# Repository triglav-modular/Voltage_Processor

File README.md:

# Triglav Modular Voltage Processor
Eurorack voltage processor / ring modulator inspired by the Buchla 257.

Features:

* Two independent channels, each mixing an attenuverter, a voltage-controlled crossfader and an offset voltage (0-5V).
* „Ring” switches turn the crossfaders into ring modulators / bipolar VCAs.
* S-curve attenuverters for easier nulling.
* Can be trimmed precisely for 1V/oct signals
* LEDs indicating negative/positive voltage.

Other notes:
* Crossfader expects a 0-8V envelope in regular mode.
* Turning on the ring switch normalizes an inverted copy of the inputs into each other. This allows the crossfader to be used as a second attenuverter, a bipolar VCA or a ring modulator with adjustable bias without any additonal patching.
* 11 HP, compact design
* Panel + PCB sandwich, suitable for skiffs
* Reverse polarity protection
* Open source

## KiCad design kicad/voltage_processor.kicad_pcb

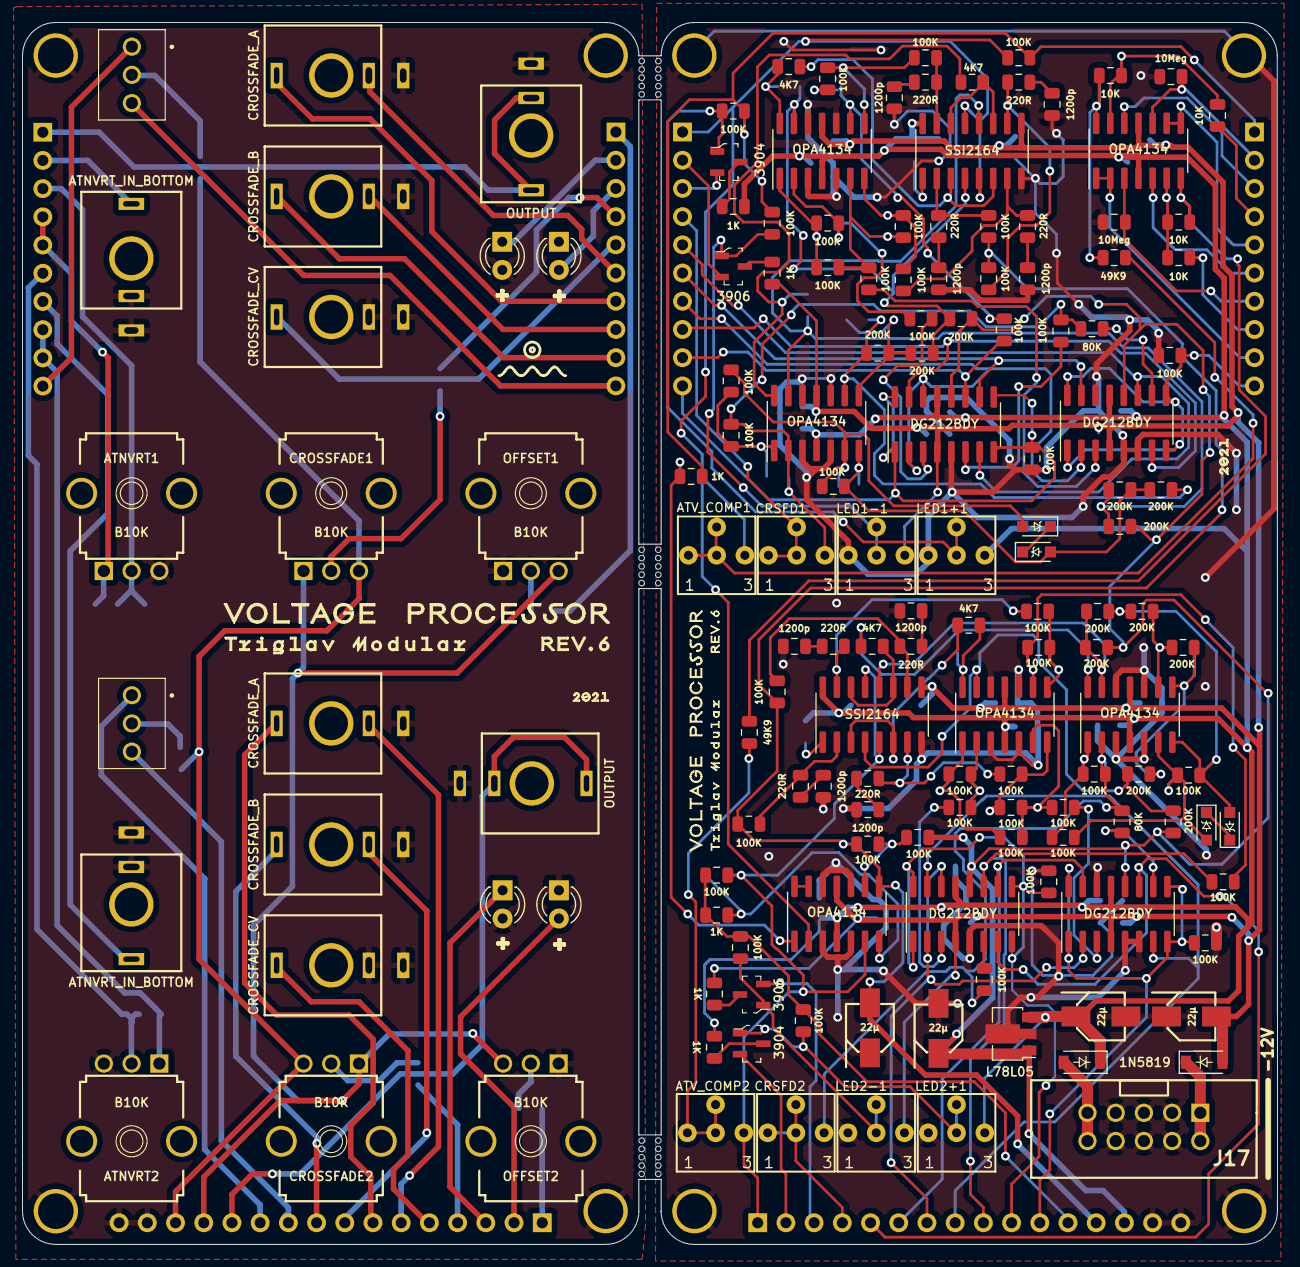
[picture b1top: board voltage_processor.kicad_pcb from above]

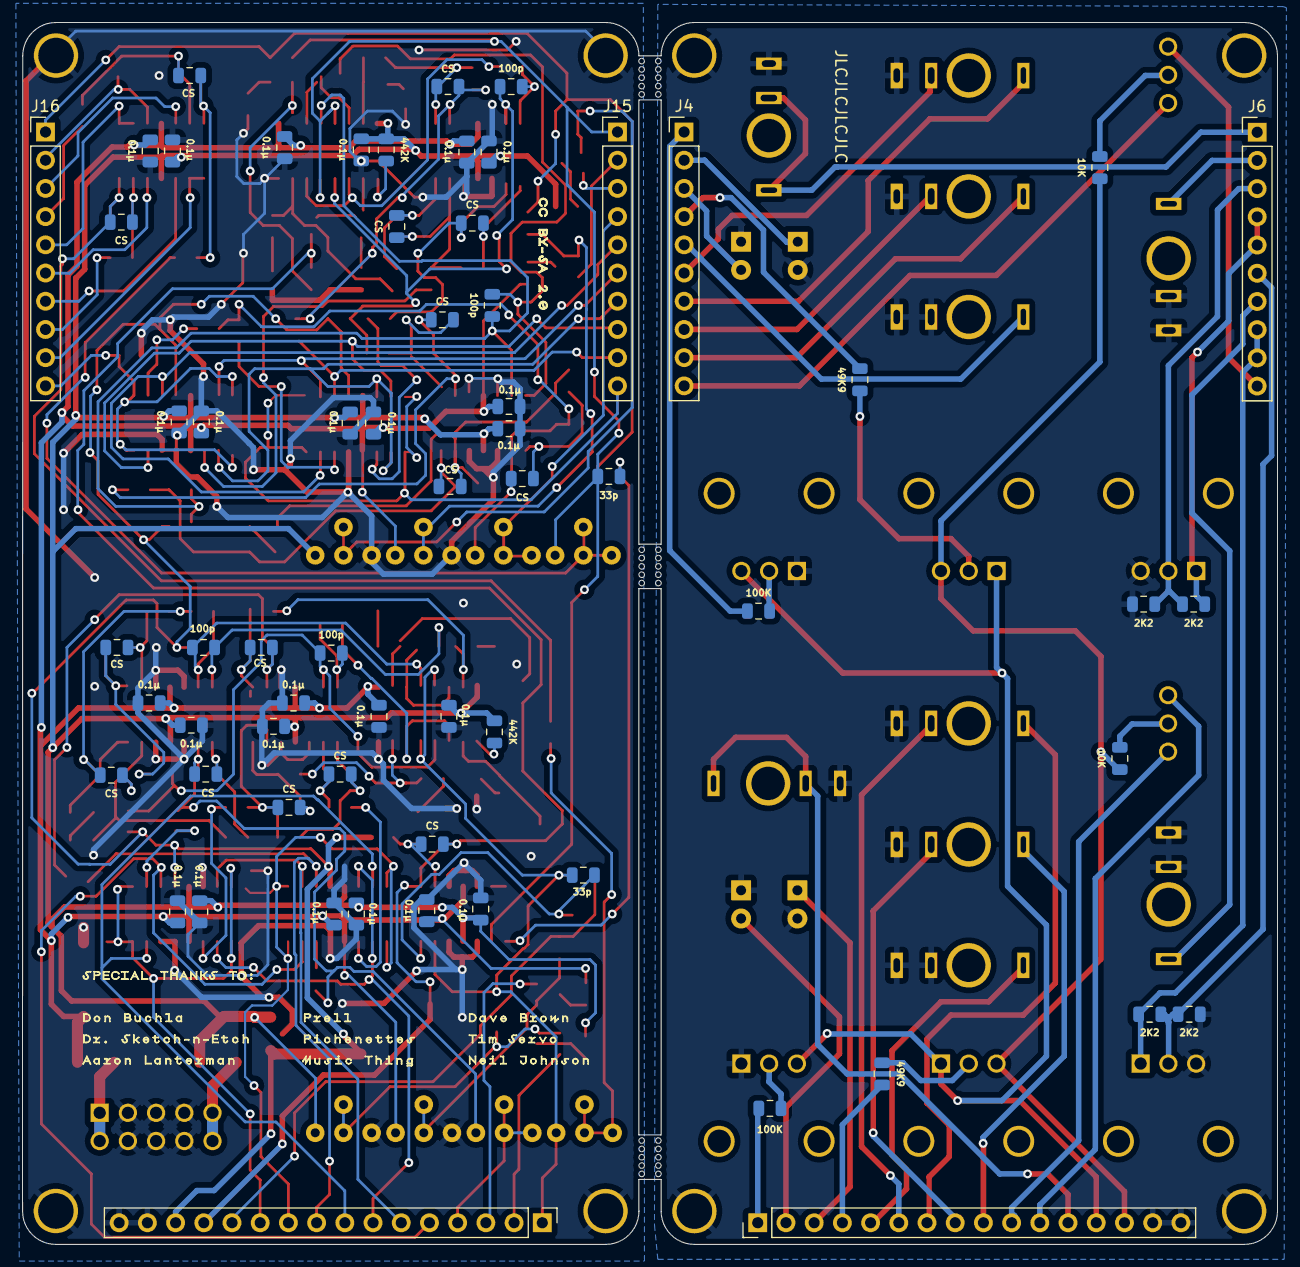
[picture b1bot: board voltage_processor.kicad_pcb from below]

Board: 2 copper layers, 113.0 x 110.0 mm, 222 parts (63 on the bottom side), 160 nets.

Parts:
ATNVRT1, ATNVRT2: B10K; MusicThingModular-9MM_SNAP-IN_POT
ATV_COMP1, ATV_COMP2: 100K; BOURNS_3362P_TRIMMER
C1, C2, C3, C4: 22µ; CAPAE430X610N
C5, C6, C18, C19, C20, C21, C22, C23, C24, C25, C35, C36, C37, C38, C45, C46, C51, C52, C55, C56, C61, C62, C67, C68: 0.1µ; C_0805_2012Metric
C7, C8, C17, C42, C43, C47, C48, C49, C50, C58, C59, C63, C64, C65, C66: CS; C_0805_2012Metric
C10, C12, C27, C29: 100p; C_0805_2012Metric
C11, C13, C14, C15, C28, C30, C31, C32: 1200p; C_0805_2012Metric
C54, C70: 33p; C_0805_2012Metric
CROSSFADE1, CROSSFADE2: B10K; MusicThingModular-9MM_SNAP-IN_POT
CRSFD1, CRSFD2: 100K; BOURNS_3362P_TRIMMER
D1, D2: 1N5819; D_SOD-123
D3, D4, D5, D6: LED; LED_D3.0mm
D7, D8, D9, D10: Z-5V; D_SOD-323_HandSoldering_ZENER
IC1, IC2, IC3, IC4: DG212BDY; SOIC-16_3.9x9.9mm_P1.27mm
J1, J2: ATNVRT_IN_BOTTOM; THONKICONN
J3: Conn_01x16_Female; PinHeader_1x16_P2.54mm_Vertical
J4, J6: Conn_01x10_Female; PinHeader_1x10_P2.54mm_Vertical
J5: Conn_01x16_Male; PinHeader_1x16_P2.54mm_Vertical
J7, J11: CROSSFADE_CV; THONKICONN
J8, J12: CROSSFADE_A; THONKICONN
J9, J13: CROSSFADE_B; THONKICONN
J10, J14: OUTPUT; THONKICONN
J15, J16: Conn_01x10_Male; PinHeader_1x10_P2.54mm_Vertical
J17: 30310-6002HB; SHDR10W64P254_2X5_2030X878X930P
LED1+1, LED1-1, LED2+1, LED2-1: 100K; BOURNS_3362P_TRIMMER
MH1, MH2, MH3, MH4, MH5, MH6, MH7, MH8: MountingHole_3.2mm_M3
OFFSET1, OFFSET2: B10K; MusicThingModular-9MM_SNAP-IN_POT
Q1, Q3: 3906; SOT-23-3
Q2, Q4: 3904; SOT-23-3
R1, R2, R3, R4: 2K2; R_0805_2012Metric
R5, R6, R7, R8, R89, R104: 10K; R_0805_2012Metric
R9, R32: 10Meg; R_0805_2012Metric
R10, R11, R12, R13, R15, R18, R19, R22, R24, R26, R27, R29, R34, R35, R38, R40, R41, R42, R43, R46, R47, R50, R51, R52, R53, R54, R56, R59, R60, R62, R63, R65, R67, R68, R70, R73, R75, R76, R82, R87, R88, R95, R102, R103: 100K; R_0805_2012Metric
R14, R16, R17, R20, R23, R25, R55, R57, R58, R61, R64, R66: 200K; R_0805_2012Metric
R21, R44, R48, R49, R85, R90: 1K; R_0805_2012Metric
R28, R30, R31, R33, R69, R71, R72, R74: 220R; R_0805_2012Metric
R36, R39: 80K; R_0805_2012Metric
R37, R45, R78, R96: 49K9; R_0805_2012Metric
R105, R106, R108, R109: 4K7; R_0805_2012Metric
R107, R110: 442K; R_0805_2012Metric
S1, S2: 108-2MS1T1B1M2QE-EVX; 1082MS1T1B1M2QEEVX
U1, U4, U5, U8, U9, U11: OPA4134; SOIC-14_3.9x8.7mm_P1.27mm
U2: L78L05; SOT-89-3
U6, U10: SSI2164; SOIC-16_3.9x9.9mm_P1.27mm
mouse-bite-2mm-slot_1, mouse-bite-2mm-slot_2, mouse-bite-2mm-slot_3: VAL**; mouse-bite-2mm-slot

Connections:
+5V: C1.1, IC1.12 (VL), IC2.12 (VL), IC3.12 (VL), IC4.12 (VL), J5.14, R16.2, R25.2, R40.2, R57.2, R66.2, U2.1 (OUT)
+12V: C3.1, C5.1, C18.1, C20.1, C22.1, C35.1, C37.1, C45.1, C46.2, C51.1, C61.1, C62.2, C67.1, D1.1 (K), IC1.13 (V+), IC2.13 (V+), IC3.13 (V+), IC4.13 (V+), LED1+1.3, LED2+1.3, R49.1, R90.1, R107.2, R110.2, U1.4 (V+), U2.3 (IN), U4.4 (V+), U5.4 (V+), U6.16 (V+), U8.4 (V+), U9.4 (V+), U10.16 (V+), U11.4 (V+)
-5V: C2.2, C17.1, J5.13, R29.2, R34.2, R43.1, R70.2, R75.2, U11.8
-12V: C4.2, C6.1, C19.1, C21.1, C23.1, C24.1, C25.1, C36.1, C38.1, C52.1, C55.1, C56.1, C68.1, D2.2 (A), IC1.4 (V-), IC2.4 (V-), IC3.4 (V-), IC4.4 (V-), LED1-1.3, LED2-1.3, R44.1, R85.1, U1.11 (V-), U4.11 (V-), U5.11 (V-), U6.9 (V-), U8.11 (V-), U9.11 (V-), U10.9 (V-), U11.11 (V-)
/Voltage Processor A/ATNVRT_1_M: J16.5, R6.2
/Voltage Processor A/ATNVRT_1_P: ATNVRT1.1 (A), J6.5, J6.6, R3.1
/Voltage Processor A/ATNVRT_2_M: J16.4, U1.12 (+)
/Voltage Processor A/ATNVRT_2_P: ATNVRT1.2 (S), J6.4, R3.2, R4.1
/Voltage Processor A/BUFF_M: J16.3, R32.1, U1.10 (+)
/Voltage Processor A/BUFF_O_M: J16.6, U1.8, U1.9 (-)
/Voltage Processor A/BUFF_P: J2.3, J6.3
/Voltage Processor A/CROSSFADE_A: IC1.2 (D1), IC1.14 (S2), IC2.2 (D1), J15.7
/Voltage Processor A/CROSSFADE_A_NORMAL: IC2.3 (S1), R19.2
/Voltage Processor A/CROSSFADE_A_RING: IC1.3 (S1), R11.2
/Voltage Processor A/CROSSFADE_B: IC1.11 (S3), J15.9, R18.2
/Voltage Processor A/CRSFD_A_1_M: IC1.10 (D3), IC2.15 (D2), J15.6
/Voltage Processor A/CRSFD_A_1_P: J4.6, J8.2
/Voltage Processor A/CRSFD_A_2_P: J4.7, J8.3
/Voltage Processor A/CRSFD_B_1_M: IC1.15 (D2), IC2.7 (D4), J15.8
/Voltage Processor A/CRSFD_B_1_P: J4.8, J9.2
/Voltage Processor A/CRSFD_B_2_P: J4.9, J9.3
/Voltage Processor A/CRSFD_CV_M: IC1.7 (D4), IC2.11 (S3), J15.5
/Voltage Processor A/CRSFD_CV_NORMAL: IC2.10 (D3), R39.2
/Voltage Processor A/CRSFD_CV_P: J4.5, J7.3
/Voltage Processor A/CRSFD_CV_RING: IC1.6 (S4), R38.1
/Voltage Processor A/CRSFD_POT_M: CRSFD1.1, CRSFD1.2, J15.4
/Voltage Processor A/CRSFD_POT_P: J4.4, R96.1
/Voltage Processor A/LED_NEG_M: J15.2, Q3.2 (E)
/Voltage Processor A/LED_NEG_P: D3.1 (K), J4.2
/Voltage Processor A/LED_POS_M: J15.3, Q4.2 (E)
/Voltage Processor A/LED_POS_P: D4.2 (A), J4.3
/Voltage Processor A/OFFSET_M: ATV_COMP1.3, C70.2, J15.1, R46.2, U6.5 (I_OUT2), U6.13 (I_OUT4), U11.2 (-)
/Voltage Processor A/OFFSET_P: J4.1, R76.2
/Voltage Processor A/OUTPUT_M: J16.2, R41.2, R46.1, R47.2, R48.1
/Voltage Processor A/OUTPUT_P: J6.2, J10.2, J10.3
/Voltage Processor A/RING_OFF: IC2.1 (IN1), IC2.8 (IN4), IC2.9 (IN3), IC2.16 (IN2), J16.1, R103.2
/Voltage Processor A/RING_OFF_P: J6.1, S2.1
/Voltage Processor A/RING_ON: IC1.1 (IN1), IC1.8 (IN4), IC1.9 (IN3), IC1.16 (IN2), J15.10, R73.2
/Voltage Processor A/RING_ON_P: J4.10, S2.3
/Voltage Processor B/ATNVRT_1_M: J16.9, R5.2
/Voltage Processor B/ATNVRT_1_P: ATNVRT2.1 (A), J6.9, J6.10, R1.1
/Voltage Processor B/ATNVRT_2_M: J16.7, U1.5 (+)
/Voltage Processor B/ATNVRT_2_P: ATNVRT2.2 (S), J6.7, R1.2, R2.1
/Voltage Processor B/BUFF_M: J16.8, R9.1, U1.3 (+)
/Voltage Processor B/BUFF_O_M: J16.10, U1.1, U1.2 (-)
/Voltage Processor B/BUFF_P: J1.3, J6.8
/Voltage Processor B/CROSSFADE_A: IC3.2 (D1), IC3.14 (S2), IC4.2 (D1), J5.7
/Voltage Processor B/CROSSFADE_A_NORMAL: IC4.3 (S1), R60.2
/Voltage Processor B/CROSSFADE_A_RING: IC3.3 (S1), R52.2
/Voltage Processor B/CROSSFADE_B: IC3.11 (S3), J5.9, R59.2
/Voltage Processor B/CRSFD_A_1_M: IC3.10 (D3), IC4.15 (D2), J5.6
/Voltage Processor B/CRSFD_A_1_P: J3.6, J12.2
/Voltage Processor B/CRSFD_A_2_P: J3.7, J12.3
/Voltage Processor B/CRSFD_B_1_M: IC3.15 (D2), IC4.7 (D4), J5.8
/Voltage Processor B/CRSFD_B_1_P: J3.8, J13.2
/Voltage Processor B/CRSFD_B_2_P: J3.9, J13.3
/Voltage Processor B/CRSFD_CV_M: IC3.7 (D4), IC4.11 (S3), J5.5
/Voltage Processor B/CRSFD_CV_NORMAL: IC4.10 (D3), R36.2
/Voltage Processor B/CRSFD_CV_P: J3.5, J11.3
/Voltage Processor B/CRSFD_CV_RING: IC3.6 (S4), R35.1
/Voltage Processor B/CRSFD_POT_M: CRSFD2.1, CRSFD2.2, J5.4
/Voltage Processor B/CRSFD_POT_P: J3.4, R45.1
/Voltage Processor B/LED_NEG_M: J5.3, Q1.2 (E)
/Voltage Processor B/LED_NEG_P: D5.1 (K), J3.3
/Voltage Processor B/LED_POS_M: J5.2, Q2.2 (E)
/Voltage Processor B/LED_POS_P: D6.2 (A), J3.2
/Voltage Processor B/OFFSET_M: ATV_COMP2.3, C54.2, J5.1, R87.2, U10.5 (I_OUT2), U10.13 (I_OUT4), U11.6 (-)
/Voltage Processor B/OFFSET_P: J3.1, R42.2
/Voltage Processor B/OUTPUT_M: J5.12, R21.1, R82.2, R87.1, R88.2
/Voltage Processor B/OUTPUT_P: J3.12, J14.2, J14.3
/Voltage Processor B/RING_OFF: IC4.1 (IN1), IC4.8 (IN4), IC4.9 (IN3), IC4.16 (IN2), J5.11, R62.2
/Voltage Processor B/RING_OFF_P: J3.11, S1.1
/Voltage Processor B/RING_ON: IC3.1 (IN1), IC3.8 (IN4), IC3.9 (IN3), IC3.16 (IN2), J5.10, R50.2
/Voltage Processor B/RING_ON_P: J3.10, S1.3
GND: C1.2, C2.1, C3.2, C4.1, C5.2, C6.2, C11.1, C13.1, C14.1, C15.1, C18.2, C19.2, C20.2, C21.2, C22.2, C23.2, C24.2, C25.2, C28.1, C30.1, C31.1, C32.1, C35.2, C36.2, C37.2, C38.2, C45.2, C46.1, C51.2, C52.2, C55.2, C56.2, C61.2, C62.1, C67.2, C68.2, IC1.5 (GND), IC2.5 (GND), IC2.6 (S4), IC2.14 (S2), IC3.5 (GND), IC4.5 (GND), IC4.6 (S4), IC4.14 (S2), J5.15, J5.16, J17.3, J17.4, J17.5, J17.6, J17.7, J17.8, LED1+1.1, LED1-1.1, LED2+1.1, LED2-1.1, R9.2, R32.2, R50.1, R62.1, R73.1, R103.1, U2.2 (GND), U4.3 (+), U4.5 (+), U4.10 (+), U4.12 (+), U5.3 (+), U5.5 (+), U5.10 (+), U5.12 (+), U6.8 (GND), U8.3 (+), U8.5 (+), U8.10 (+), U8.12 (+), U9.3 (+), U9.5 (+), U9.10 (+), U9.12 (+), U10.8 (GND), U11.3 (+), U11.5 (+), U11.10 (+), U11.12 (+)
GND1: ATNVRT1.3 (E), ATNVRT2.3 (E), D3.2 (A), D4.1 (K), D5.2 (A), D6.1 (K), J1.1, J1.2, J2.1, J2.2, J3.15, J3.16, J7.1, J7.2, J8.1, J9.1, J10.1, J11.1, J11.2, J12.1, J13.1, J14.1, OFFSET1.1 (A), OFFSET2.1 (A), R2.2, R4.2
unnamed: ATV_COMP1.1, ATV_COMP1.2, R37.1
unnamed: ATV_COMP2.1, ATV_COMP2.2, R78.1
unnamed: C7.1, R8.1, R37.2, U1.14
unnamed: C7.2, R6.1, R8.2, U1.13 (-)
unnamed: C8.1, R7.1, R78.2, U1.7
unnamed: C8.2, R5.1, R7.2, U1.6 (-)
unnamed: C10.1, R109.2, U4.14
unnamed: C10.2, R14.1, R16.1, U4.13 (-), U6.12 (I_OUT3)
unnamed: C11.2, R28.2
unnamed: C12.1, R108.1, U5.14
unnamed: C12.2, R23.1, R25.1, U5.13 (-), U6.4 (I_OUT1)
unnamed: C13.2, R30.2
unnamed: C14.2, R31.2
unnamed: C15.2, R33.2
unnamed: C17.2, R40.1, R43.2, U11.9 (-)
unnamed: C27.1, R106.2, U8.14
unnamed: C27.2, R55.1, R57.1, U8.13 (-), U10.12 (I_OUT3)
unnamed: C28.2, R69.2
unnamed: C29.1, R105.1, U9.14
unnamed: C29.2, R64.1, R66.1, U9.13 (-), U10.4 (I_OUT1)
unnamed: C30.2, R71.2
unnamed: C31.2, R72.2
unnamed: C32.2, R74.2
unnamed: C42.1, R51.1, R53.2, U8.1
unnamed: C42.2, CRSFD2.3, R35.2, R36.1, R51.2, U8.2 (-)
unnamed: C43.1, R54.1, R95.2, U9.1
unnamed: C43.2, R52.1, R54.2, U9.2 (-)
unnamed: C47.1, D7.2 (A), R55.2, R56.1, R58.2, U8.7
unnamed: C47.2, D8.2 (A), R53.1, R56.2, U8.6 (-)
unnamed: C48.1, R61.1, R64.2, U8.8
unnamed: C48.2, R58.1, R61.2, U8.9 (-)
unnamed: C49.1, R63.1, R67.2, U9.8
unnamed: C49.2, R59.1, R63.2, U9.9 (-)
unnamed: C50.1, R65.1, R68.2, U9.7
unnamed: C50.2, R60.1, R65.2, R95.1, U9.6 (-)
unnamed: C54.1, R21.2, U11.7
unnamed: C58.1, R10.1, R12.2, U4.1
unnamed: C58.2, CRSFD1.3, R10.2, R38.2, R39.1, U4.2 (-)
unnamed: C59.1, R13.1, R102.2, U5.1
unnamed: C59.2, R11.1, R13.2, U5.2 (-)
unnamed: C63.1, D9.2 (A), R14.2, R15.1, R17.2, U4.7
unnamed: C63.2, D10.2 (A), R12.1, R15.2, U4.6 (-)
unnamed: C64.1, R20.1, R23.2, U4.8
unnamed: C64.2, R17.1, R20.2, U4.9 (-)
unnamed: C65.1, R22.1, R26.2, U5.8
unnamed: C65.2, R18.1, R22.2, U5.9 (-)
unnamed: C66.1, R24.1, R27.2, U5.7
unnamed: C66.2, R19.1, R24.2, R102.1, U5.6 (-)
unnamed: C70.1, R48.2, U11.1
unnamed: CROSSFADE1.2 (S), R96.2
unnamed: CROSSFADE2.2 (S), R45.2
unnamed: D1.2 (A), J17.9, J17.10
unnamed: D2.1 (K), J17.1, J17.2
unnamed: D7.1 (K), D8.1 (K)
unnamed: D9.1 (K), D10.1 (K)
unnamed: LED1+1.2, Q4.1 (B), R47.1
unnamed: LED1-1.2, Q3.1 (B), R41.1
unnamed: LED2+1.2, Q2.1 (B), R88.1
unnamed: LED2-1.2, Q1.1 (B), R82.1
unnamed: OFFSET1.2 (S), R76.1
unnamed: OFFSET2.2 (S), R42.1
unnamed: Q1.3 (C), R85.2
unnamed: Q2.3 (C), R90.2
unnamed: Q3.3 (C), R44.2
unnamed: Q4.3 (C), R49.2
unnamed: R26.1, R28.1, U6.15 (I_IN4)
unnamed: R27.1, R30.1, U6.7 (I_IN2)
unnamed: R29.1, R31.1, U6.10 (I_IN3)
unnamed: R33.1, R34.1, U6.2 (I_IN1)
unnamed: R67.1, R69.1, U10.15 (I_IN4)
unnamed: R68.1, R71.1, U10.7 (I_IN2)
unnamed: R70.1, R72.1, U10.10 (I_IN3)
unnamed: R74.1, R75.1, U10.2 (I_IN1)
unnamed: R89.1, S1.2 (COM)
unnamed: R104.1, S2.2 (COM)
unnamed: R105.2, U10.3 (VC1), U10.6 (VC2)
unnamed: R106.1, U10.11 (VC3), U10.14 (VC4)
unnamed: R107.1, U10.1 (MODE)
unnamed: R108.2, U6.3 (VC1), U6.6 (VC2)
unnamed: R109.1, U6.11 (VC3), U6.14 (VC4)
unnamed: R110.1, U6.1 (MODE)
unnamed: U11.13 (-), U11.14
PANEL_+5V: CROSSFADE1.3 (E), CROSSFADE2.3 (E), J3.14, R89.2, R104.2
PANEL_-5V: CROSSFADE1.1 (A), CROSSFADE2.1 (A), J3.13, OFFSET1.3 (E), OFFSET2.3 (E)

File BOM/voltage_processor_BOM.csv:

"Id";"Designator";"Package";"Quantity";"Designation";"Supplier and ref";
1;"R26,R68,R75,R22,R102,R63,R103,R10,R19,R15,R52,R38,R18,R88,R13,R51,R27,R70,R50,R67,R12,R35,R56,R54,R62,R40,R43,R24,R29,R59,R65,R87,R41,R82,R11,R60,R53,R73,R47,R34,R95,R46,R76,R42";"R_0805_2012Metric";44;"100K";;;
2;"R78,R37,R45,R96";"R_0805_2012Metric";4;"49K9";;;
3;"ATV_COMP2,CRSFD2,ATV_COMP1,LED1+1,LED2+1,LED2-1,LED1-1,CRSFD1";"BOURNS_3362P_TRIMMER";8;"100K";;;
4;"R58,R61,R16,R23,R25,R55,R66,R17,R20,R64,R14,R57";"R_0805_2012Metric";12;"200K";;;
5;"IC3,IC2,IC4,IC1";"SOIC-16_3.9x9.9mm_P1.27mm";4;"DG212BDY";;;
6;"J10,J14";"THONKICONN";2;"OUTPUT";;;
7;"J7,J11";"THONKICONN";2;"CROSSFADE_CV";;;
8;"R72,R69,R28,R71,R30,R33,R74,R31";"R_0805_2012Metric";8;"220R";;;
9;"C1,C4,C3,C2";"CAPAE430X610N";4;"22µ";;;
10;"C31,C30,C15,C28,C32,C11,C13,C14";"C_0805_2012Metric";8;"1200p";;;
11;"OFFSET2,OFFSET1,ATNVRT2,ATNVRT1,CROSSFADE2,CROSSFADE1";"MusicThingModular-9MM_SNAP-IN_POT";6;"B10K";;;
12;"D6,D3,D4,D5";"LED_D3.0mm";4;"LED";;;
13;"MH8,MH7,MH4,MH2,MH5,MH3,MH6,MH1";"MountingHole_3.2mm_M3";8;"MountingHole_3.2mm_M3";;;
14;"R7,R8,R5,R6,R89,R104";"R_0805_2012Metric";6;"10K";;;
15;"R21,R90,R48,R49,R44,R85";"R_0805_2012Metric";6;"1K";;;
16;"J1,J2";"THONKICONN";2;"ATNVRT_IN_BOTTOM";;;
17;"R106,R105,R109,R108";"R_0805_2012Metric";4;"4K7";;;
18;"J17";"SHDR10W64P254_2X5_2030X878X930P";1;"30310-6002HB";;;
19;"U1,U9,U8,U11,U4,U5";"SOIC-14_3.9x8.7mm_P1.27mm";6;"OPA4134";;;
20;"D7,D8,D9,D10";"D_SOD-323_HandSoldering_ZENER";4;"Z-5V";;;
21;"R36,R39";"R_0805_2012Metric";2;"80K";;;
22;"Q3,Q1";"SOT-23-3";2;"3906";;;
23;"R32,R9";"R_0805_2012Metric";2;"10Meg";;;
24;"mouse-bite-2mm-slot_3,mouse-bite-2mm-slot_2,mouse-bite-2mm-slot_1";"mouse-bite-2mm-slot";3;"VAL**";;;
25;"U10,U6";"SOIC-16_3.9x9.9mm_P1.27mm";2;"SSI2164";;;
26;"Q4,Q2";"SOT-23-3";2;"3904";;;
27;"J9,J13";"THONKICONN";2;"CROSSFADE_B";;;
28;"D1,D2";"D_SOD-123";2;"1N5819";;;
29;"J12,J8";"THONKICONN";2;"CROSSFADE_A";;;
30;"S1,S2";"1082MS1T1B1M2QEEVX";2;"108-2MS1T1B1M2QE-EVX";;;
31;"U2";"SOT-89-3";1;"L78L05";;;
32;"C25,C62,C46,C68,C56,C36,C23,C52,C21,C55,C22,C35,C20,C61,C24,C6,C67,C37,C45,C38,C5,C18,C51,C19";"C_0805_2012Metric";24;"0.1µ";;;
33;"C8,C42,C66,C7,C43,C50,C63,C65,C64,C59,C17,C47,C48,C49,C58";"C_0805_2012Metric";15;"CS";;;
34;"R4,R2,R3,R1";"R_0805_2012Metric";4;"2K2";;;
35;"J5";"PinHeader_1x16_P2.54mm_Vertical";1;"Conn_01x16_Male";;;
36;"J6,J4";"PinHeader_1x10_P2.54mm_Vertical";2;"Conn_01x10_Female";;;
37;"R110,R107";"R_0805_2012Metric";2;"442K";;;
38;"J15,J16";"PinHeader_1x10_P2.54mm_Vertical";2;"Conn_01x10_Male";;;
39;"C27,C10,C29,C12";"C_0805_2012Metric";4;"100p";;;
40;"J3";"PinHeader_1x16_P2.54mm_Vertical";1;"Conn_01x16_Female";;;
41;"C54,C70";"C_0805_2012Metric";2;"33p";;;

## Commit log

2021-05-29 gitignore
2021-05-29 panel fixes
2021-05-29 front panel fixes
2021-05-31 fixes
